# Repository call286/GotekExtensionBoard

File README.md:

# GotekExtensionBoard

External board initally meant to provide an extrenal board for Goteks in Amiga 500.
* 2 Boards
  * internal board to connect to the gotek and other internal hardware
  * external board to connect display, switches, rotary etc.
* boards connect via fpc to help with nondestructive mods for the case
* fpc can be routed through the air gaps in the case

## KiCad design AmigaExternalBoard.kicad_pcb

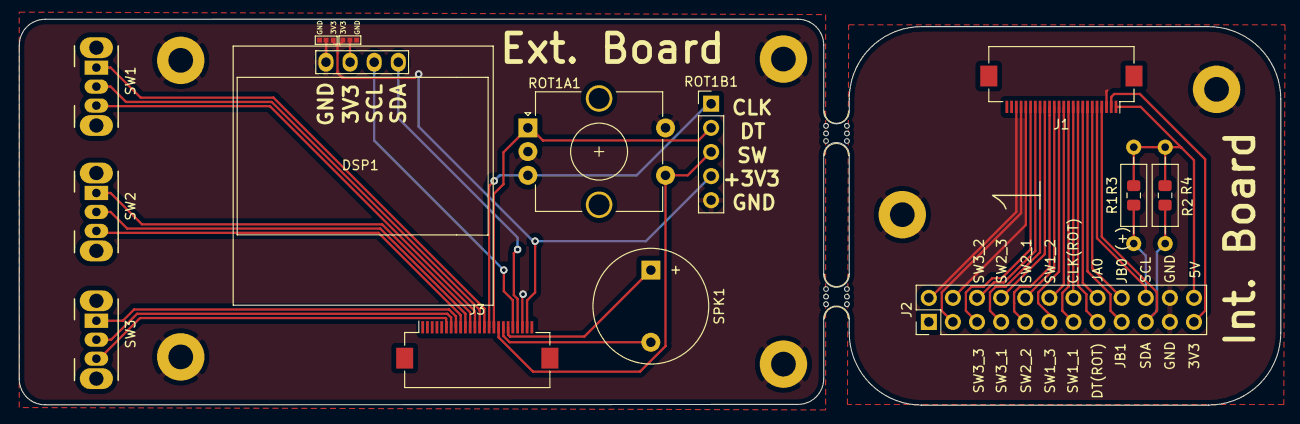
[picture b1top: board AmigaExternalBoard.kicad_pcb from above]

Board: 2 copper layers, 132.9 x 40.7 mm, 18 parts (0 on the bottom side), 24 nets.

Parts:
DSP1: SSD1306; 128x64OLED
J1, J3: Conn_01x24; Hirose_FH12-24S-0.5SH_1x24-1MP_P0.50mm_Horizontal
J2: Conn_01x24; PinHeader_2x12_P2.54mm_Vertical
JP1, JP2: Jumper_3_Open; SolderJumper-3_P0.5mm_Open_Pad0.5x0.5mm
R1: R-OptionalPullup-SCL; R_Axial_DIN0207_L6.3mm_D2.5mm_P10.16mm_Horizontal
R2: R-OptionalPullup-SDA; R_Axial_DIN0207_L6.3mm_D2.5mm_P10.16mm_Horizontal
R3: R-OptionalPullup-SCL; R_0805_2012Metric_Pad1.15x1.40mm_HandSolder
R4: R-OptionalPullup-SDA; R_0805_2012Metric_Pad1.15x1.40mm_HandSolder
ROT1A1: Rotary_Encoder_Switch; RotaryEncoder_Alps_EC12E-Switch_Vertical_H20mm_CircularMoun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
ROT1B1: Conn_01x05; PinHeader_1x05_P2.54mm_Vertical
SPK1: Speaker; Buzzer_12x9.5RM7.6
SW1, SW2, SW3: SW_SPDT; SW_CuK_OS102011MA1QN1_SPDT_Angled
mouse-bite-2.54mm-slot, mouse-bite-2.54mm-slot#2: VAL**; mouse-bite-2.54mm-slot

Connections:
+3V3: J1.2, J2.23, J3.23, JP1.1, JP2.1, ROT1B1.4
+5V: J1.1, J2.24, J3.24, R1.1, R2.1, R3.1, R4.1
CLK(ROT): J1.10, J2.14, J3.15, ROT1A1.B, ROT1B1.1
DT(ROT): J1.9, J2.15, J3.16, ROT1A1.A, ROT1B1.2
GND: J1.3, J2.21, J2.22, J3.22, JP1.3, JP2.3, ROT1A1.C, ROT1A1.S1, ROT1B1.5
GotekBTN1: J1.20, J2.4, J3.5
GotekBTN2: J1.21, J2.3, J3.4
GotekLED: J1.22, J2.2, J3.3
JA0(ROT-SW): J1.8, J2.16, J3.17, ROT1A1.S2, ROT1B1.3
JB0(SPK): J1.6, J2.18, J3.19, SPK1.1
JB1(SPK): J1.7, J2.17, J3.18, SPK1.2
unnamed: DSP1.1, JP1.2
unnamed: DSP1.2, JP2.2
SCL(DSP): DSP1.3, J1.5, J2.20, J3.20, R1.2, R3.2
SDA(DSP): DSP1.4, J1.4, J2.19, J3.21, R2.2, R4.2
SW1_1: J1.11, J2.13, J3.14, SW1.1
SW1_2: J1.12, J2.12, J3.13, SW1.2
SW1_3: J1.13, J2.11, J3.12, SW1.3
SW2_1: J1.14, J2.10, J3.11, SW2.1
SW2_2: J1.15, J2.9, J3.10, SW2.2
SW2_3: J1.16, J2.8, J3.9, SW2.3
SW3_1: J1.17, J2.7, J3.8, SW3.1
SW3_2: J1.18, J2.6, J3.7, SW3.2
SW3_3: J1.19, J2.5, J3.6, SW3.3

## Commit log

2021-04-24 Minimal Version
2021-04-24 Switches added
2021-08-07 Modified AmigaExternalBoard-cache.lib Modified AmigaExternalBoard.kicad_pcb Modified AmigaExternalBoard.sch Added .gitignore Added AmigaExternalBoard-rescue.dcm Added AmigaExternalBoard-rescue.lib Ad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
2021-08-07 Modified AmigaExternalBoard.kicad_pcb Modified AmigaExternalBoard.kicad_pcb-bak Modified AmigaExternalBoard.sch Modified AmigaExternalBoard.sch-bak
2021-11-29 Modified AmigaExternalBoard-cache.lib Modified AmigaExternalBoard.kicad_pcb Modified AmigaExternalBoard.kicad_pcb-bak Modified AmigaExternalBoard.sch Modified AmigaExternalBoard.sch-bak Modified fp-i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
2022-07-22 2022-07-22
2022-07-22 Cleanup
2022-07-22 Picture
